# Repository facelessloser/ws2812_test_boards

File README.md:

# ws2812_test_boards
ws2812_test_boards

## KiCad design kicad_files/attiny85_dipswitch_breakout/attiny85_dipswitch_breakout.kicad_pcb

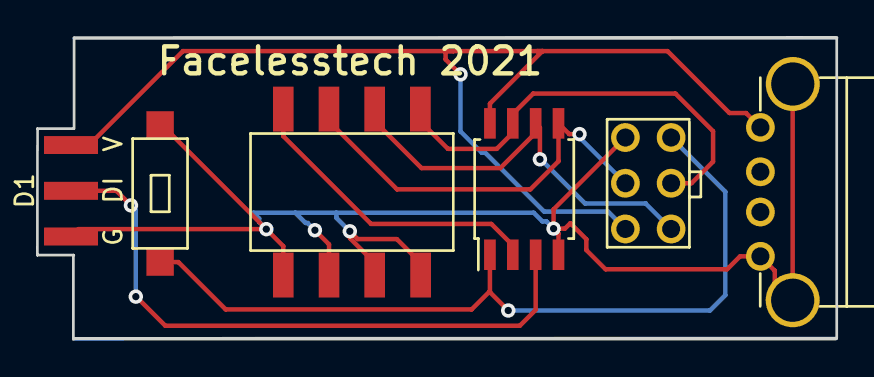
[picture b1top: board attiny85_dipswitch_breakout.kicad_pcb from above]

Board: 2 copper layers, 44.4 x 16.7 mm, 6 parts (0 on the bottom side), 8 nets.

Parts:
D1: WS2812B; ws2812_header_custom_smd_strip
J1: USB_A; male_usb_custom
J2: AVR-ISP-6; ISP_6pin_small_custom
SW1: SW_Push; SMD_2pin_button_custom
U1: ATtiny85-20SU; SOIJ-8_5.3x5.3mm_P1.27mm
U3: 4_pos_dip_smd

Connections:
unnamed: D1.1, J1.1, J2.2, U1.8
unnamed: D1.3, J1.4, J2.6, SW1.1, U1.4, U3.1, U3.2, U3.3, U3.4
unnamed: D1.4, U1.3
unnamed: J2.1, U1.6, U3.7
unnamed: J2.3, U1.7, U3.8
unnamed: J2.4, U1.5, U3.6
unnamed: J2.5, SW1.2, U1.1
unnamed: U1.2, U3.5

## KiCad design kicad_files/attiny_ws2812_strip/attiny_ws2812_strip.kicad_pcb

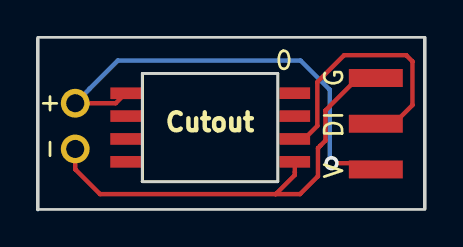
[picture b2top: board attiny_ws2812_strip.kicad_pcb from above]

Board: 2 copper layers, 21.5 x 9.5 mm, 3 parts (0 on the bottom side), 3 nets.

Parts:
D1: WS2812B; ws2812_header_custom_smd_strip
U1: battery_custom; vcc_gnd_2pin_custom
U2: ATtiny85-20SU; attiny85_arduino_enbedded

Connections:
unnamed: D1.1, U1.2, U2.8
unnamed: D1.3, U1.1, U2.4
unnamed: D1.4, U2.3

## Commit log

2021-04-05 3d print files
2021-04-05 PCB kicad files
2021-04-07 added arduino code
